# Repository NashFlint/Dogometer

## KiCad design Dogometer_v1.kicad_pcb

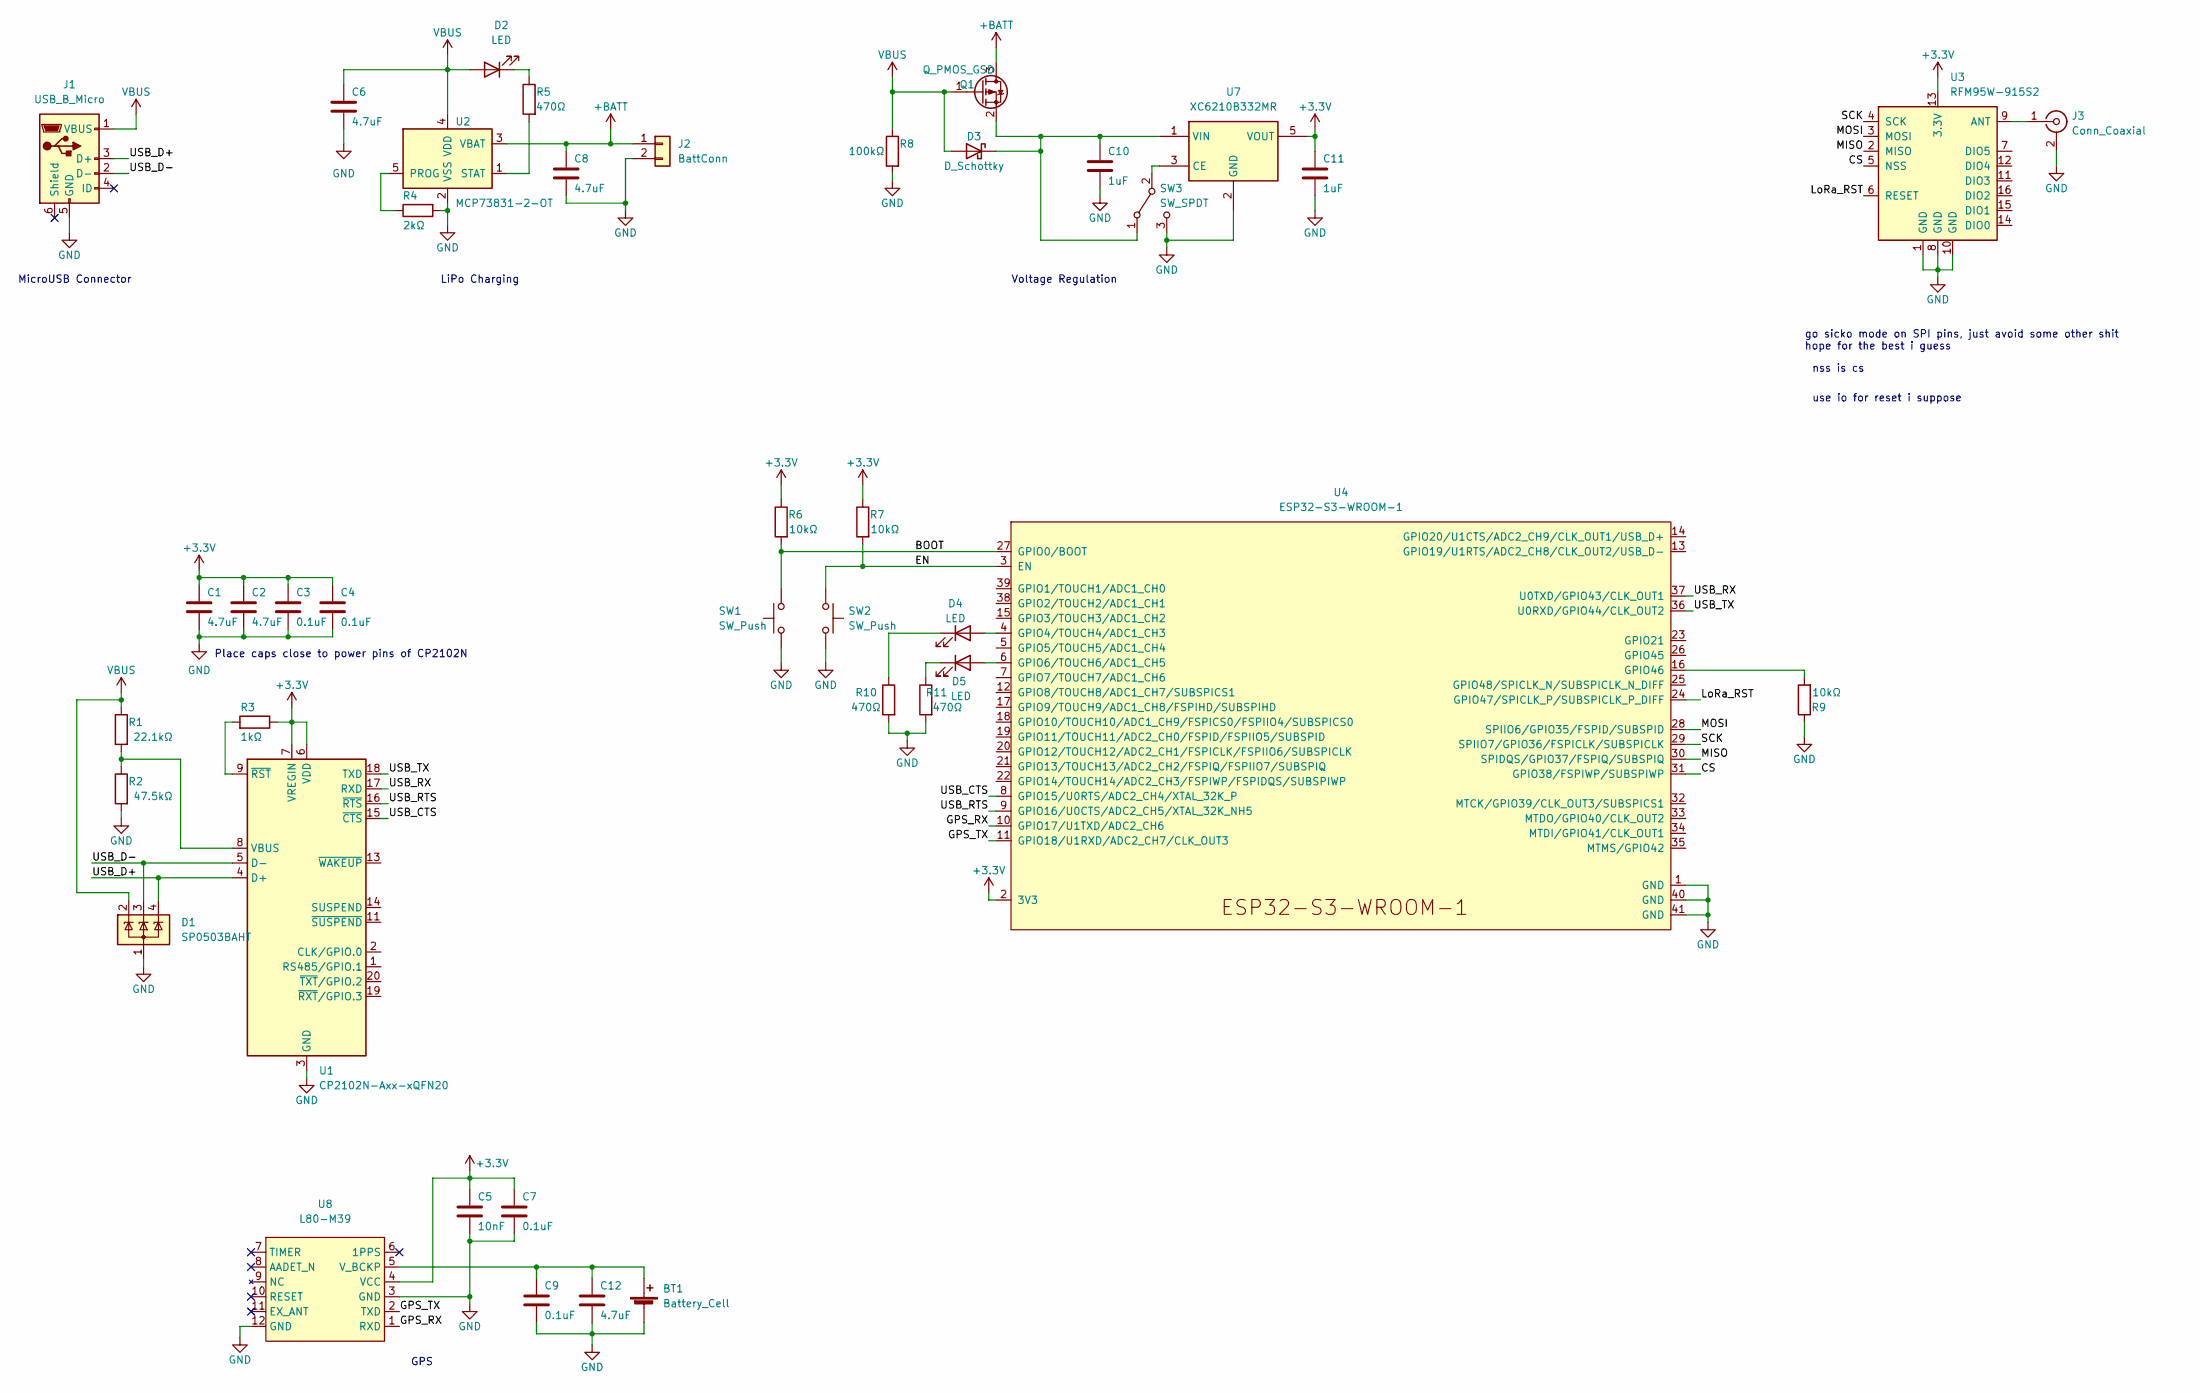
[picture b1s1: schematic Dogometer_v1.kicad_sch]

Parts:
BT1: Battery_Cell; BatteryHolder_Keystone_3000_1x12mm
C1, C2: 4.7uF; C_0402_1005Metric
C3, C4: 0.1uF; C_0402_1005Metric
C5: 10nF; C_0603_1608Metric
C6, C8, C12: 4.7uF; C_0603_1608Metric
C7, C9: 0.1uF; C_0603_1608Metric
C10, C11: 1uF; C_0603_1608Metric
D1: SP0503BAHT; SOT-143
D2, D4, D5: LED; LED_0603_1608Metric
D3: D_Schottky; D_SOD-323
J1: USB_B_Micro; USB_Micro-B_Amphenol_10118194_Horizontal
J2: BattConn; JST_PH_S2B-PH-K_1x02_P2.00mm_Horizontal
J3: Conn_Coaxial; SMA_Molex_73251-2120_EdgeMount_Horizontal
Q1: Q_PMOS_GSD; SOT-23
R1: 22.1kΩ; R_0402_1005Metric
R2: 47.5kΩ; R_0402_1005Metric
R3: 1kΩ; R_0402_1005Metric
R4: 2kΩ; R_0603_1608Metric
R5, R10, R11: 470Ω; R_0603_1608Metric
R6, R7, R9: 10kΩ; R_0603_1608Metric
R8: 100kΩ; R_0603_1608Metric
SW1, SW2: SW_Push; SW-SMD-GT-TC029B-H025-L1N
SW3: SW_SPDT; SW-TH_SK12D07VG4
U1: CP2102N-Axx-xQFN20; SiliconLabs_QFN-20-1EP_3x3mm_P0.5mm_EP1.8x1.8mm
U2: MCP73831-2-OT; SOT-23-5
U3: RFM95W-915S2; HOPERF_RFM9XW_SMD
U4: ESP32-S3-WROOM-1
U7: XC6210B332MR; SOT-23-5
U8: L80-M39; L80 - M39

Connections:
+3.3V: C1.1, C2.1, C3.1, C4.1, C5.1, C7.1, C11.1, R3.1, R6.1, R7.1, U1.6 (VDD), U1.7 (VREGIN), U3.13 (3.3V), U4.2 (3V3), U7.5 (VOUT), U8.4 (VCC)
+BATT: C8.1, J2.1, Q1.3 (D), U2.3 (VBAT)
/BOOT: R6.2, SW1.2, U4.27 (GPIO0/BOOT); also elsewhere on the board
/CS: U3.5 (NSS), U4.31 (GPIO38/FSPIWP/SUBSPIWP)
/EN: R7.2, SW2.1, U4.3 (EN); also elsewhere on the board
/GPS_RX: U4.10 (GPIO17/U1TXD/ADC2_CH6), U8.1 (RXD)
/GPS_TX: U4.11 (GPIO18/U1RXD/ADC2_CH7/CLK_OUT3), U8.2 (TXD)
/LoRa_RST: U3.6 (RESET), U4.24 (GPIO47/SPICLK_P/SUBSPICLK_P_DIFF)
/MISO: U3.2 (MISO), U4.30 (SPIDQS/GPIO37/FSPIQ/SUBSPIQ)
/MOSI: U3.3 (MOSI), U4.28 (SPIIO6/GPIO35/FSPID/SUBSPID)
/SCK: U3.4 (SCK), U4.29 (SPIIO7/GPIO36/FSPICLK/SUBSPICLK)
/USB_CTS: U1.15 (~CTS), U4.8 (GPIO15/U0RTS/ADC2_CH4/XTAL_32K_P)
/USB_D+: D1.4 (K), J1.3 (D+), U1.4 (D+)
/USB_D-: D1.3 (K), J1.2 (D-), U1.5 (D-)
/USB_RTS: U1.16 (~RTS), U4.9 (GPIO16/U0CTS/ADC2_CH5/XTAL_32K_NH5)
/USB_RX: U1.17 (RXD), U4.37 (U0TXD/GPIO43/CLK_OUT1)
/USB_TX: U1.18 (TXD), U4.36 (U0RXD/GPIO44/CLK_OUT2)
GND: BT1.2 (-), C1.2, C2.2, C3.2, C4.2, C5.2, C6.2, C7.2, C8.2, C9.2, C10.2, C11.2, C12.2, D1.1 (A), J1.5 (GND), J2.2, J3.2 (Ext), R2.2, R4.2, R8.2, R9.1, R10.2, R11.2, SW1.1, SW2.2, SW3.3 (C), U1.3 (GND), U1.12 (GND), U1.21 (GND), U2.2 (VSS), U3.1 (GND), U3.8 (GND), U3.10 (GND), U4.1 (GND), U4.40 (GND), U4.41 (GND), U7.2 (GND), U8.3 (GND), U8.12 (GND); also elsewhere on the board
unnamed: BT1.1 (+), C9.1, C12.1, U8.5 (V_BCKP)
unnamed 19: C10.1, D3.1 (K), Q1.2 (S), SW3.1 (A), U7.1 (VIN); also elsewhere on the board
unnamed: D2.1 (K), R5.1
unnamed: D4.1 (K), R10.1
unnamed: D4.2 (A), U4.4 (GPIO4/TOUCH4/ADC1_CH3)
unnamed: D5.1 (K), R11.1
unnamed: D5.2 (A), U4.6 (GPIO6/TOUCH6/ADC1_CH5)
unnamed: J3.1 (In), U3.9 (ANT)
unnamed: R1.2, R2.1, U1.8 (VBUS)
unnamed: R3.2, U1.9 (~RST)
unnamed: R4.1, U2.5 (PROG)
unnamed: R5.2, U2.1 (STAT)
unnamed: R9.2, U4.16 (GPIO46)
unnamed 31: SW3.2 (B), U7.3 (CE); also elsewhere on the board
VBUS: C6.1, D1.2 (K), D2.2 (A), D3.2 (A), J1.1 (VBUS), Q1.1 (G), R1.1, R8.1, U2.4 (VDD)

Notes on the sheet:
nss is cs
GPS
Place caps close to power pins of CP2102N
Voltage Regulation
MicroUSB Connector
go sicko mode on SPI pins, just avoid some other shit hope for the best i guess
LiPo Charging
use io for reset i suppose

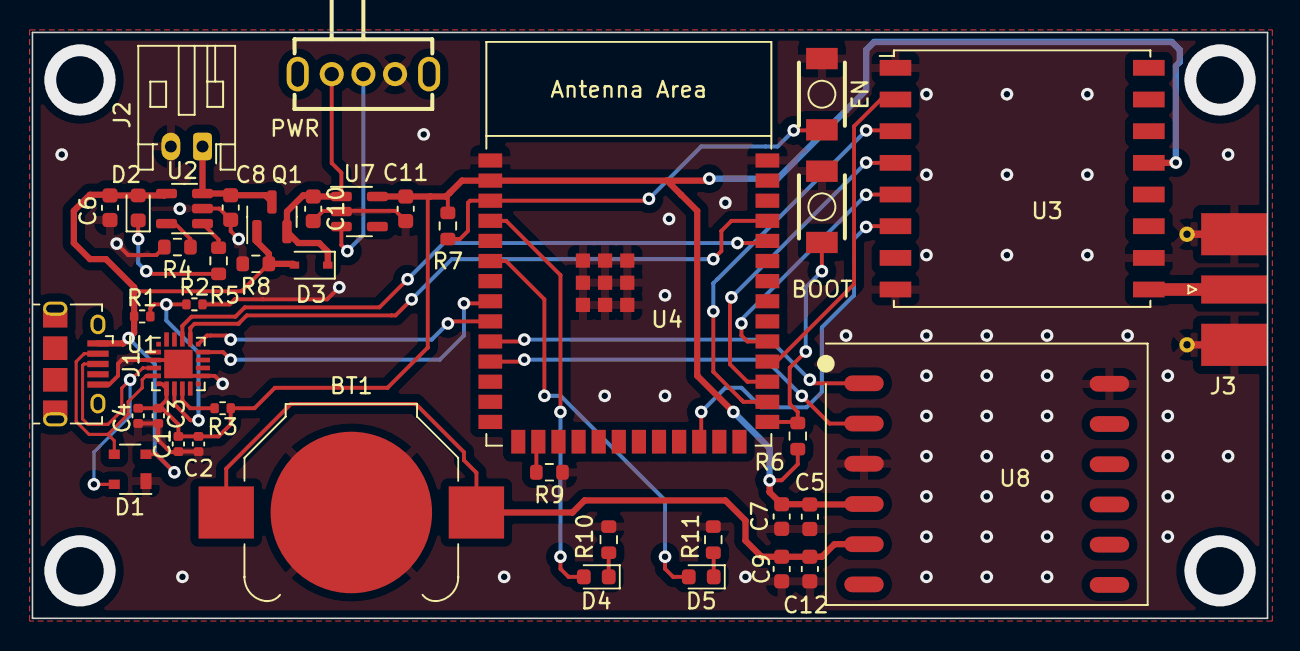
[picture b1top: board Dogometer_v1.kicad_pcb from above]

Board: 2 copper layers, 78.0 x 37.0 mm, 42 parts (0 on the bottom side), 33 nets.

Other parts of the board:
BOOT: SW_Push; SW-SMD-GT-TC029B-H025-L1N
EN: SW_Push; SW-SMD-GT-TC029B-H025-L1N
PWR: SW_SPDT; SW-TH_SK12D07VG4

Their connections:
/BOOT: BOOT.2; also elsewhere on the board
/EN: EN.1; also elsewhere on the board
GND: BOOT.1, EN.2, PWR.3 (C); also elsewhere on the board
unnamed 19: PWR.1 (A); also elsewhere on the board
unnamed 31: PWR.2 (B); also elsewhere on the board

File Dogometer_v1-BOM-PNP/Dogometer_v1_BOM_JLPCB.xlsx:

Value | Designator | Footprint | JLCPCB Part #
Battery_Cell | BT1 | BatteryHolder_Keystone_3000_1x12mm
4.7uF | C1, C2 | C_0402 | C106859
0.1uF | C3, C4 | C_0402 | C60474
10nF | C5 | C_0603 | C100042
4.7uF | C6, C8, C12 | C_0603 | C109456
0.1uF | C7, C9 | C_0603 | C14663
1uF | C10, C11 | C_0603 | C14664
SP0503BAHT | D1 | SOT-143 | C7074
LED | D2 | LED_0603 | C2286
LED | D4 | LED_0603 | C434423
LED | D5 | LED_0603 | C72041
D_Schottky | D3 | SOD-323 | C191023
USB_B_Micro | J1 | USB_Micro-B_Amphenol_10118194_Horizontal | C132563
BattConn | J2 | JST_PH_S2B-PH-K_1x02_P2.00mm_Horizontal
Conn_Coaxial | J3 | SMA_Molex_73251-2120_EdgeMount_Horizontal
Q_PMOS_GSD | Q1 | SOT-23 | C192664
22.1K | R1 | R_0402 | C2693020
47.5K | R2 | R_0402 | C100449
1K | R3 | R_0402 | C328304
2K | R4 | R_0603 | C394539
470 | R5, R10, R11 | R_0603 | C176130
10K | R6, R7, R9 | R_0603 | C101254
100K | R8 | R_0603 | C881354
SW_Push | SW1, SW2 | SW-SMD-GT-TC029B-H025-L1N | C843669
SW_SPDT | SW3 | SW-TH_SK12D07VG4 | C393937
CP2102N-Axx-xQFN20 | U1 | SiliconLabs_QFN-20-1EP_3x3mm_P0.5mm_EP1.8x1.8mm | C969913
MCP73831-2-OT | U2 | SOT-23-5 | C424093
RFM95W-915S2 | U3 | HOPERF_RFM9XW_SMD | C2844473
ESP32-S3-WROOM-1 | U4 | ESP32-S3-WROOM-1 | C2913198
XC6210B332MR | U7 | SOT-23-5 | C424705
L80-M39 | U8 | L80 - M39 | C133488
Collated Components:
